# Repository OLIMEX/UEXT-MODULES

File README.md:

# UEXT-MODULES
OSHW UEXT modules

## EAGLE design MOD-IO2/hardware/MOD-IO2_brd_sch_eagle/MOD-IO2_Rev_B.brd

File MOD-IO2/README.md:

# MOD-IO2

**Input output expandable board with UEXT**

MOD-IO2 is a stackable development board which adds RELAYs and GPIOs to any of our development boards with UEXT.
If you work with any of our development boards with a [UEXT connector](https://www.olimex.com/Products/Modules/UEXT) and you need more GPIOs and/or RELAY outputs, you can add these by connecting MOD-IO2 to your development board.
This board gives you an easy way to interface up to 2 relays and 7 GPIOs.
MOD-IO2 is stackable and addressable, but what does this mean?
These boards can stack together so you can add as many inputs and outputs as you want!
E.g. 2-4-6-8 etc.!
MOD-IO2 has a PIC16F1503 microcontroller and the firmware is available for modification.

[Purchase your MOD-IO2 here!](https://www.olimex.com/Products/Modules/IO/MOD-IO2/open-source-hardware)

## FEATURES

- PIC16F1503 microcontroller
- Pre-loaded open-source firmware for easier interfacing, especially with Linux-enabled boards
- ICSP 6-pin connector for in-circuit programming with PIC-KIT3 or other compatible programmer/debugger.
- 9-pin terminal screw connector for 7 GPIOs, 3.3V and GND
- PWR jack for 12VDC
- 7 GPIOs which could implement different functionality as PWM, SPI, I2C, ANALOG IN/OUT etc.
- 2 relay outputs with 15A/250VAC contacts with screw terminals
- RELAY output status LEDs
- Four mounting holes - 3.3mm ~ (0.13)"
- FR-4, 1.5mm ~ (0.062)", soldermask, white silkscreen component print
- Dimensions 61x52mm ~ (2.4 x 2.05)"

## DOCUMENTS

- [MOD-IO2 user manual](doc/MOD-IO2.pdf)

## HARDWARE

- [MOD-IO2 schematic](hardware/MOD-IO2-Rev-B-schematic.pdf)
- [MOD-IO2 schematic and board layout sources for Eagle](hardware/MOD-IO2_brd_sch_eagle)

## SOFTWARE

- [MOD-IO2 firmware version 3.02](software/MOD-IO2_firmware_v_3_02)
- [Linux tool for controlling MOD-IO2](https://github.com/OLIMEX/OLINUXINO/tree/master/SOFTWARE/UEXT%20MODULES/MOD-IO2/linux-access-tool)
- [Arduino IDE library for MOD-IO2 + OLIMEXINO-328](software/OLIMEXINO-328+MOD-IO2)
- [OLIMEXINO-STM32 and MOD-IO2 relay control](software/Olimexino-STM32_MOD-IO2)
- Older firmware, older demo software, customer projects and more at the [wiki page](https://www.olimex.com/wiki/MOD-IO2)

## FAQ

### I found a very nice example of MOD-IO2 connected to another board on the internet. It doesn't work despite using the same setup as the author. What might be different?

There are number of firmware revisions that had been released for MOD-IO2.
You should ensure the example you have found used the same firmware revision of MOD-IO2 as the one you have on the module at the moment.
Each major firmware revision uses a different board address (for firmware revisions 3, 3.1, and 3.02, it is the same - 0x21) AND DIFFERENT PROTOCOL.
Each firmware has a README file inside the source archive that is available for download.
Refer to that README or the user manual for more information about the firmware.

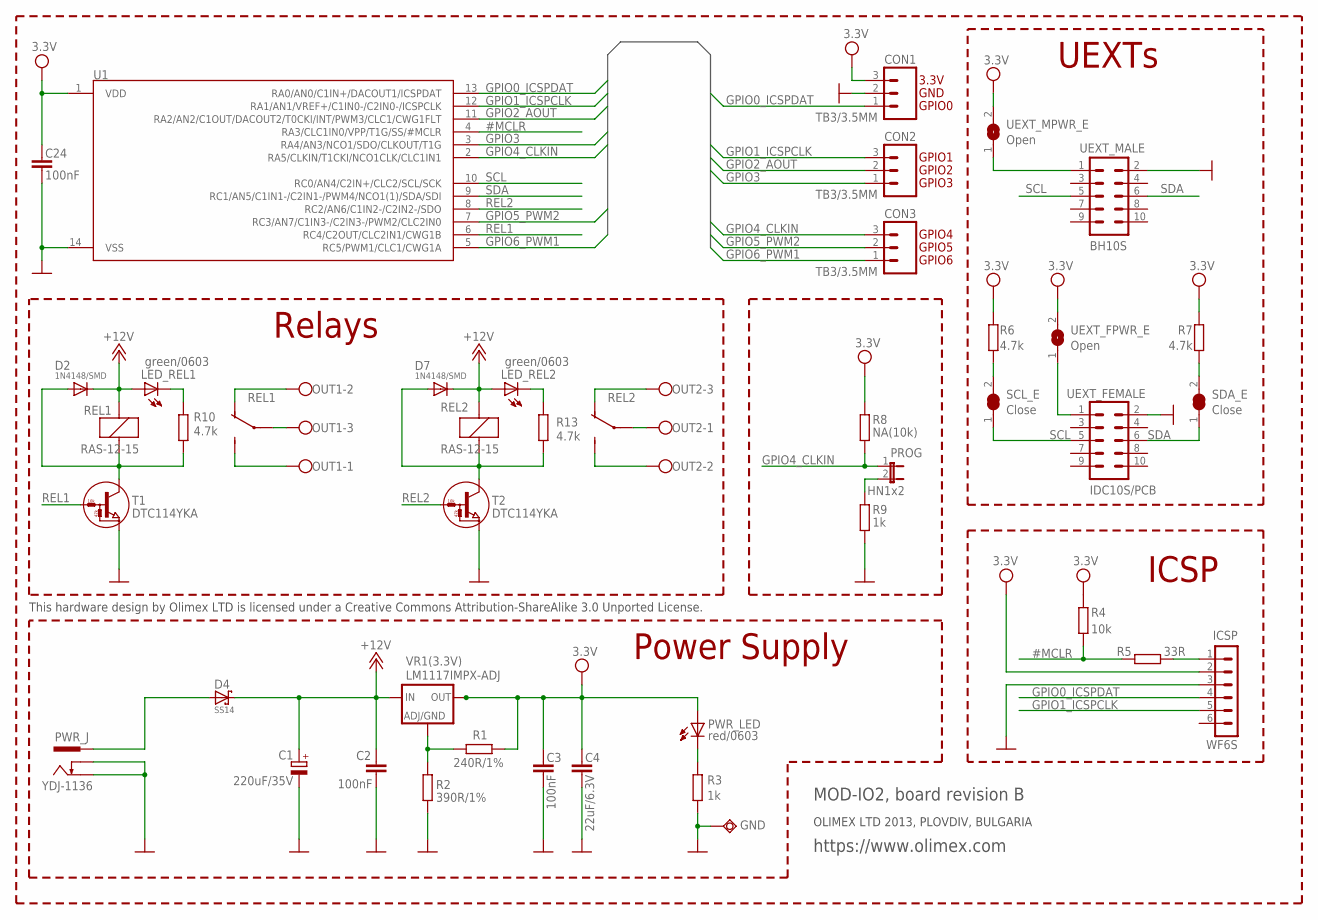
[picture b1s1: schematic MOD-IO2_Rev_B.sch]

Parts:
C1: 220uF/35V; E3,5-8
C2, C3, C24: 100nF; C0603_5MIL
C4: 22uF/6.3V; C0805_5MIL
CON1, CON2, CON3: TB3/3.5MM; CON3/3.5MM
D2, D7: 1N4148/SMD; SOD80C
D4: SS14; MLL-41
GND: TESTPAD40/70; TESTPAD
ICSP: WF6S
LED_REL1, LED_REL2: green/0603; LED-0603
OUT1, OUT2: TB3/5MM; W237-103
PROG: HN1x2; JP1
PWR_J: YDJ-1136; PWR_JACK_UNI_MILLING
PWR_LED: red/0603; LED-0603
R1: 240R/1%; R0603_5MIL
R2: 390R/1%; R0603_5MIL
R3, R9: 1k; R0603_5MIL
R4: 10k; R0603_5MIL
R5: 33R; R0603_5MIL
R6, R7, R10, R13: 4.7k; R0603_5MIL
R8: NA(10k); R0603_5MIL
REL1, REL2: RAS-12-15; H200-FAT
SCL_E: Close; SJ-CLOSE
SDA_E: Close; SJ-CLOSE
T1, T2: DTC114YKA; SOT-23
U1: PIC16F1503-I/SL; SOIC14
UEXT_FEMALE: IDC10S/PCB; ML10L_PADS_FEMAIL
UEXT_FPWR_E: Open; SJ
UEXT_MALE: BH10S; ML10_PADS
UEXT_MPWR_E: Open; SJ
VR1(3.3V): LM1117IMPX-ADJ; SOT223

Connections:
#MCLR: R4.2, R5.2, U1.4 (RA3/CLC1IN0/VPP/T1G/SS/#MCLR)
+12V: C1.+, C2.2, D2.C, D4.K (C), D7.C, LED_REL1.A, LED_REL2.A, REL1.1, REL2.1, VR1(3.3V).3 (IN)
ADJ/GND: R1.1, R2.1, VR1(3.3V).1 (ADJ/GND)
GND: C1.-, C2.1, C3.1, C4.1, C24.2, CON1.2, GND.P$1, ICSP.3, PWR_J.-, PWR_J.--, R2.2, R3.2, R9.1, T1.2 (E), T2.2 (E), U1.14 (VSS), UEXT_FEMALE.2, UEXT_MALE.2
GPIO0_ICSPDAT: CON1.1, ICSP.4, U1.13 (RA0/AN0/C1IN+/DACOUT1/ICSPDAT)
GPIO1_ICSPCLK: CON2.3, ICSP.5, U1.12 (RA1/AN1/VREF+/C1IN0-/C2IN0-/ICSPCLK)
GPIO2_AOUT: CON2.2, U1.11 (RA2/AN2/C1OUT/DACOUT2/T0CKI/INT/PWM3/CL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)
GPIO3: CON2.1, U1.3 (RA4/AN3/NCO1/SDO/CLKOUT/T1G)
GPIO4_CLKIN: CON3.3, PROG.1, R8.1, U1.2 (RA5/CLKIN/T1CKI/NCO1CLK/CLC1IN1)
GPIO5_PWM2: CON3.2, U1.7 (RC3/AN7/C1IN3-/C2IN3-/PWM2/CLC2IN0)
GPIO6_PWM1: CON3.1, U1.5 (RC5/PWM1/CLC1/CWG1A)
unnamed: OUT1.3, REL1.P
unnamed: UEXT_FEMALE.1, UEXT_FPWR_E.1
unnamed: OUT2.1, REL2.P
unnamed: OUT2.2, REL2.S
unnamed: R7.1, SDA_E.2
unnamed: R6.1, SCL_E.2
unnamed: OUT1.1, REL1.S
unnamed: PROG.2, R9.2
unnamed: UEXT_MALE.1, UEXT_MPWR_E.1
unnamed: ICSP.1, R5.1
unnamed: OUT2.3, REL2.O
unnamed: LED_REL1.C, R10.2
unnamed: OUT1.2, REL1.O
unnamed: LED_REL2.C, R13.2
unnamed: D7.A, R13.1, REL2.2, T2.3 (C)
unnamed: D2.A, R10.1, REL1.2, T1.3 (C)
unnamed: D4.A, PWR_J.+
unnamed: PWR_LED.C, R3.1
REL1: T1.1 (B), U1.6 (RC4/C2OUT/CLC2IN1/CWG1B)
REL2: T2.1 (B), U1.8 (RC2/AN6/C1IN2-/C2IN2-/SDO)
SCL: SCL_E.1, U1.10 (RC0/AN4/C2IN+/CLC2/SCL/SCK), UEXT_FEMALE.5, UEXT_MALE.5
SDA: SDA_E.1, U1.9 (RC1/AN5/C1IN1-/C2IN1-/PWM4/NCO1(1)/SDA/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), UEXT_FEMALE.6, UEXT_MALE.6
VCC: C3.2, C4.2, C24.1, CON1.3, ICSP.2, PWR_LED.A, R1.2, R4.1, R6.2, R7.2, R8.2, U1.1 (VDD), UEXT_FPWR_E.2, UEXT_MPWR_E.2, VR1(3.3V).2 (OUT), VR1(3.3V).4 (RAD)

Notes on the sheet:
ICSP
UEXTs
Power Supply
Relays
GPIO0
GPIO1
GPIO2
GPIO3
GPIO4
GPIO5
GPIO6
GND
3.3V
This hardware design by Olimex LTD is licensed under a Creative Commons Attribution-ShareAlike 3.0 Unported License.
OLIMEX LTD 2013, PLOVDIV, BULGARIA
https://www.olimex.com
MOD-IO2, board revision B

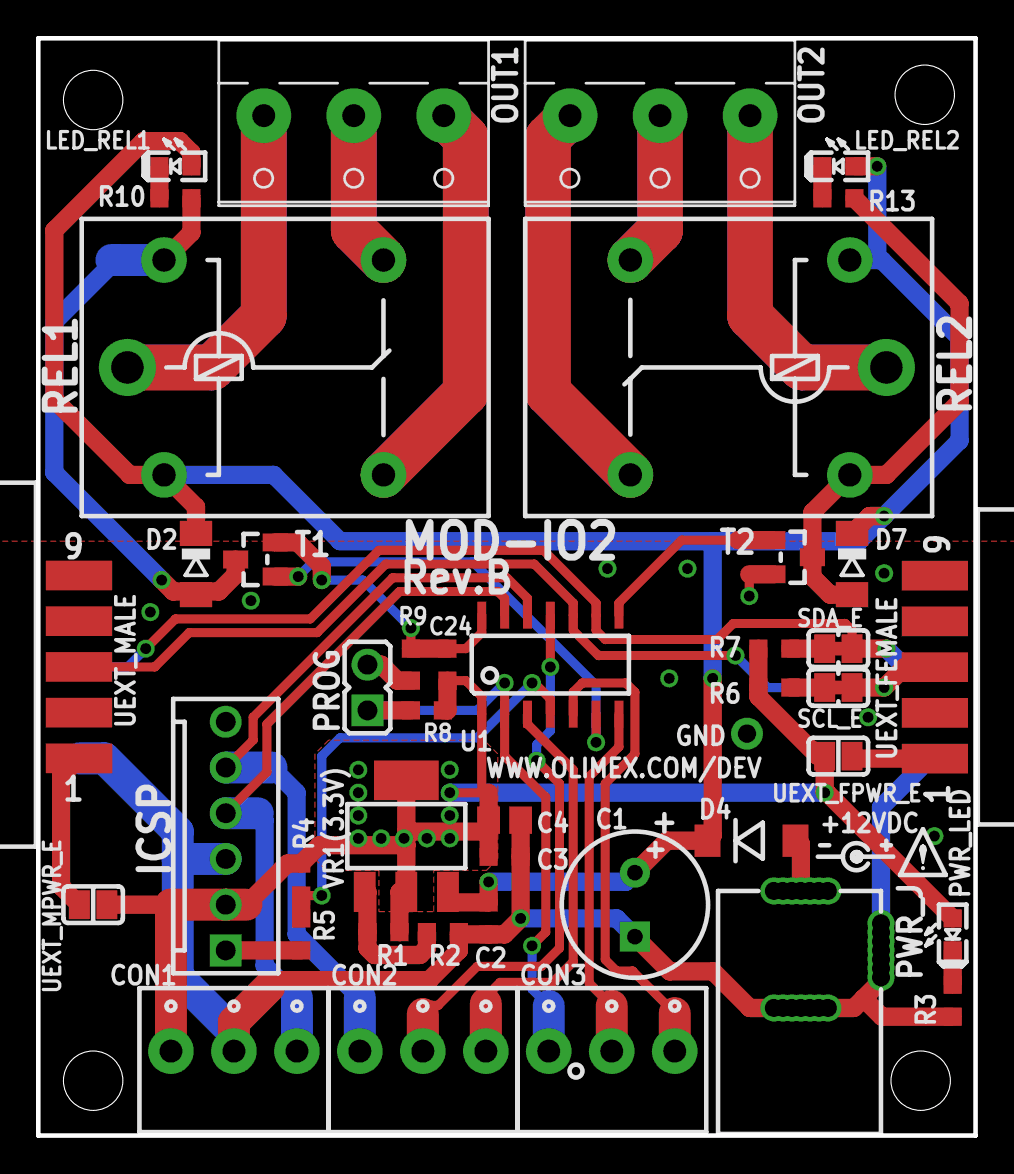
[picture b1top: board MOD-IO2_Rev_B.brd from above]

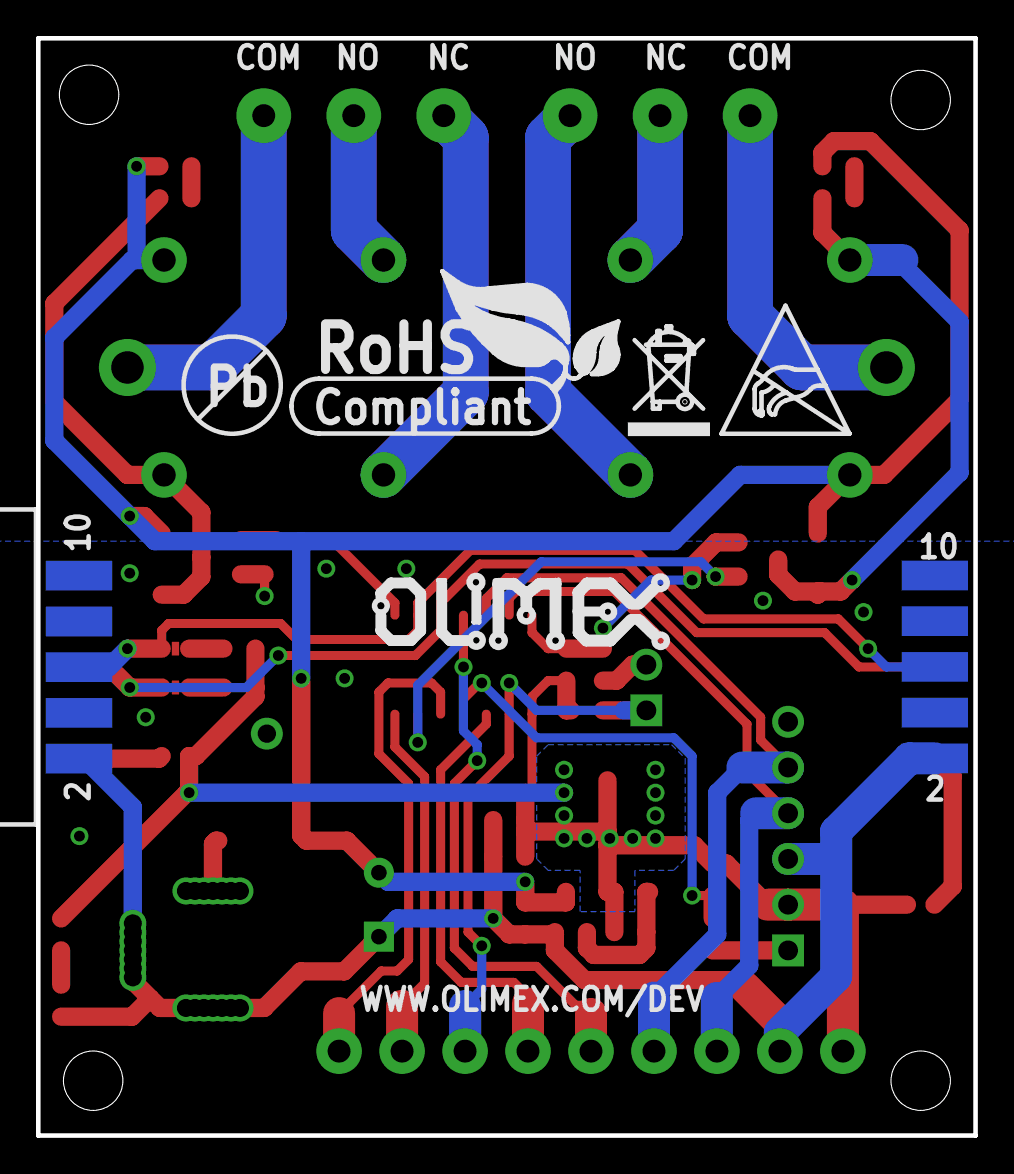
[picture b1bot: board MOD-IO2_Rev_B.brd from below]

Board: 2 copper layers, 52.1 x 61.0 mm, 49 parts (6 on the bottom side), 34 nets.

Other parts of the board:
U$1: RECYCLE_BIN1/8
U$3: ESD_SYMBOL
U$4: PB
U$5: ROHS
U$6: OLIMEX1_V
U$9: ATTENTION_SMALL

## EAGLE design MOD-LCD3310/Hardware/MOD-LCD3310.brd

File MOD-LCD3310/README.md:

MOD-LCD3310
===========

[
*MOD-LCD3310*](https://www.olimex.com/Products/Modules/LCD/MOD-LCD3310/open-source-hardware)

Hardware
--------
* Schematic in PDF format
* Schematic in Eagle format
* Board in Eagle format

Software
--------
* [**A20-OLinuXino-MICRO example**](https://github.com/OLIMEX/OLINUXINO/tree/master/SOFTWARE/A20)
* OLIMEXINO-32U4 (Arduino AVR) example
* PIC32-PINGUINO (PIC32) examples with GPIO and SPI
* OLIMEXINO-STM32 (Maple STM32) examples wigh GPIO and SPI
* NXP (LPC1227) example
* IAR (STM32) example

Licensee
--------
Apache License Version 2.0

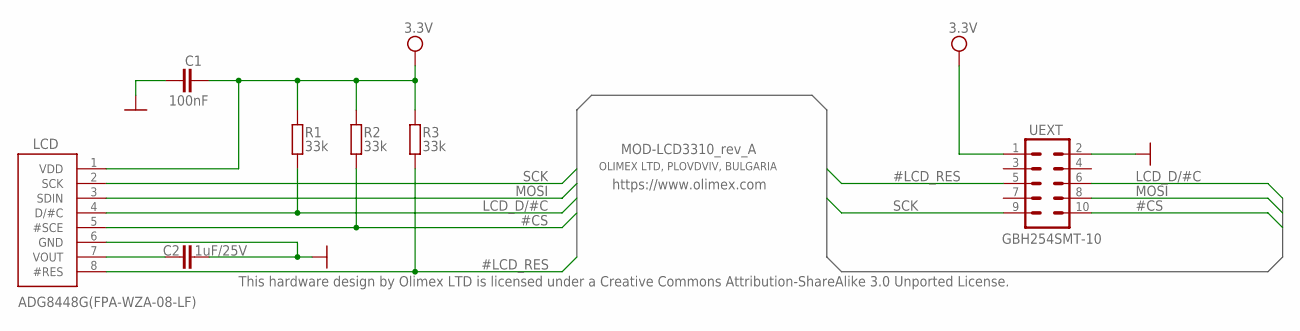
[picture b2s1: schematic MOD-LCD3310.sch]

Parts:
C1: 100nF; C0603_DWS
C2: 1uF/25V; C0805_5MIL_DWS
LCD: ADG8448G(FPA-WZA-08-LF); NOKIA_3310_LCD_CON8_EXACTLY_BOT
R1, R2, R3: 33k; R0603_5MIL_DWS
UEXT: GBH254SMT-10; ML10_S

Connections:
#CS: LCD.5 (#SCE), R2.2, UEXT.10
#LCD_RES: LCD.8 (#RES), R3.2, UEXT.5
GND: C1.2, C2.1, LCD.6 (GND), UEXT.2
LCD_D/#C: LCD.4 (D/#C), R1.2, UEXT.6
LCD_VOUT: C2.2, LCD.7 (VOUT)
MOSI: LCD.3 (SDIN), UEXT.8
SCK: LCD.2 (SCK), UEXT.9
VCC: C1.1, LCD.1 (VDD), R1.1, R2.1, R3.1, UEXT.1

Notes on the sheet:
MOD-LCD3310_rev_A
OLIMEX LTD, PLOVDVIV, BULGARIA
https://www.olimex.com
This hardware design by Olimex LTD is licensed under a Creative Commons Attribution-ShareAlike 3.0 Unported License.

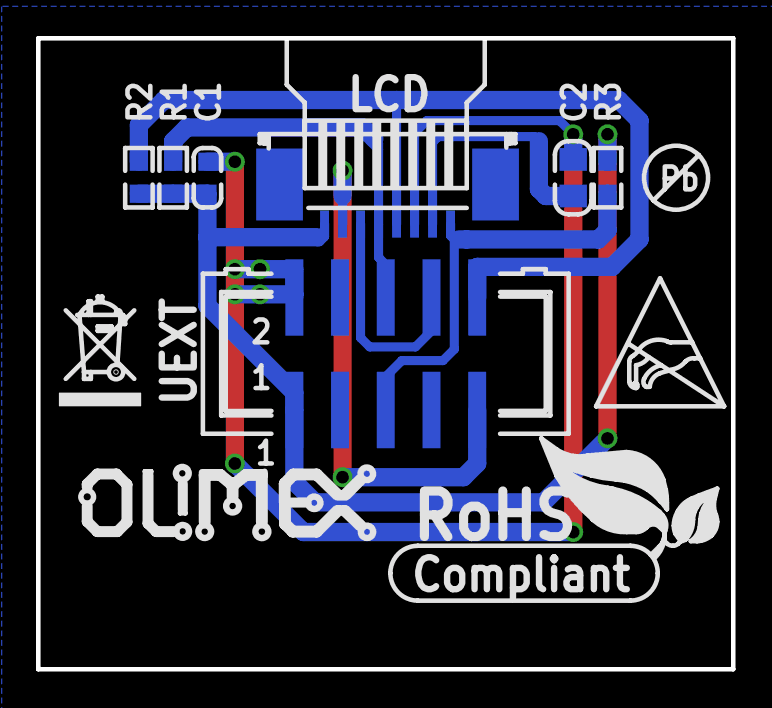
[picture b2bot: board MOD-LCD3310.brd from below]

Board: 2 copper layers, 38.6 x 35.1 mm, 12 parts (11 on the bottom side), 8 nets.

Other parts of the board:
U$1: PB_SMALL
U$2: RECYCLE_BIN1/8
U$3: ESD_SYMBOL
U$4: ROHS
U$8: OLIMEX1_V

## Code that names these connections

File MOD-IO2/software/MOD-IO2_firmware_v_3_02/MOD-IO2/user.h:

/******************************************************************************/
/* User Level #define Macros                                                  */
/******************************************************************************/

#define REL1	LATCbits.LATC4
#define REL2	LATCbits.LATC2
#define REL1_TRIS TRISCbits.TRISC4
#define REL2_TRIS TRISCbits.TRISC2


#define GPIO0_TRIS TRISAbits.TRISA0
#define GPIO0_LAT LATAbits.LATA0
#define GPIO0_PORT PORTAbits.RA0

#define GPIO1_TRIS TRISAbits.TRISA1
#define GPIO1_LAT LATAbits.LATA1
#define GPIO1_PORT PORTAbits.RA1

#define GPIO2_TRIS TRISAbits.TRISA2
#define GPIO2_LAT LATAbits.LATA2
#define GPIO2_PORT PORTAbits.RA2

#define GPIO3_TRIS TRISAbits.TRISA4
#define GPIO3_LAT LATAbits.LATA4
#define GPIO3_PORT PORTAbits.RA4

#define GPIO4_TRIS TRISAbits.TRISA5
#define GPIO4_LAT LATAbits.LATA5
#define GPIO4_PORT PORTAbits.RA5

#define GPIO5_TRIS TRISCbits.TRISC3
#define GPIO5_LAT LATCbits.LATC3
#define GPIO5_PORT PORTCbits.RC3

#define GPIO6_TRIS TRISCbits.TRISC5
#define GPIO6_LAT LATCbits.LATC5
#define GPIO6_PORT PORTCbits.RC5


#define JMP_TRIS	TRISAbits.TRISA5
#define JMP_LAT		LATAbits.LATA5
#define JMP_PORT	PORTAbits.RA5

/*--------------------------------I2C PINS--------------------------------*/
#define SCL_TRIS		TRISCbits.TRISC0
#define SCL_LAT			LATCbits.LATC0
#define SCL_PORT		PORTCbits.RC0
#define SDA_TRIS		TRISCbits.TRISC1
#define SDA_LAT			LATCbits.LATC1
#define SDA_PORT		PORTCbits.RC1

#define DEFAULT_ADDRESS		0x21
#define MEMORY_ADDRESS		0x7FF

#define START_C	0b00001000	//START CONDITION MASK
#define STOP_C	0b00010000	//STOP CONDITION MASK
#define STATE1	0b00001001	// MASTER WRITE LAST WAS ADDRESS
#define STATE2	0b00101001	// MASTER WRITE LAST WAS DATA
#define STATE3	0b00001101	// MASTER READ LAST WAS ADDRESS
#define STATE4	0b00101100	// MASTER READ LAST WAS DATA
#define STATE5	0b00101000	// MASTER NACK

#define MAX_BUFFER_SIZE		10


#define Nop() asm("NOP")


/******************************************************************************/
/* Local Variables							      */
/******************************************************************************/

extern unsigned char ADDRESS;
extern unsigned char DATA_BUFFER[6];
extern unsigned int DATA_INDEX;
extern unsigned char DATA_OUT[2];



/******************************************************************************/
/* User Function Prototypes                                                   */
/******************************************************************************/



/**
 * Initialize all the periphere
 * @param none
 */
void InitApp(void);
/**
 * Read stored address from the program memmory 0x7FF. If the cell if empty
 * the board load the default address - 0x21.
 * @param none
 */
void InitAddress(void);
/**
 * Initialize all the gpio ports. By default:
 * @LAT registers - All "0" - low level
 * @TRIS registers - All "1" - inputs
 * @WPUA registers - All pullups on PORTA are on, PORTC doesn't have such.
 * @param none
 */
void InitGPIO(void);
/**
 * Initialize interrupts. Only interrupts from I2C are processed.
 * @param none
 */
void InitInterupts(void);
/**
 * Initialize I2C module. It is configured for 100kHz, 7-bit address, with
 * enabled clock streching and enabled STOP and START interrupts.
 * @param none
 */
void InitI2C(void);
/**
 * Write procedure for writing in the program memory.
 * @param data Data to be stored, the range is from 0x0000 to 0x3FFF.
 * @param address The address of the cell in the programm memory.
 */
void WriteFlash(unsigned int data, unsigned int address);
/**
 * Read procedure for reading from the program memory.
 * @return The data in the selected cell
 * @param address The address of the cell in the program memory.
 */
unsigned int ReadFlash(unsigned int address);
/**
 * Erase the stored data in specific cell int the program memory.
 * @param address The address of the cell
 */
void EraseFlash(unsigned int address);
/**
 * By unlocking the cell becomes available for writing and erasing.
 * @param none
 */
void UnlockFlash(void);
/*
 * Defines the function of the gpio.
 * @param data - The states of all gpios bit0 - GPIO0, bit1 - GPIO1 ...
 */
void CommandSetTris(unsigned char data);
/**
 * Set output level of the gpios
 * @param data - Defines all parameters - bit0 - GPIO0, bit1 - GPIO1 ...
 */
void CommandSetLat(unsigned char data);
/**
 * Return the current state of the PORT registers.
 * @param none
 */
unsigned char CommandGetPort(void);
/**
 * Set or clear pullups. Note that not all GPIO have internal pullups.
 * @param data - bitmasked state of the all GPIOs pullups
 */
void CommandSetPullUps(unsigned char data);
/* Set state of the two relays.
 * @param data - bitmasked state of the relays - bit0 -REL1, bit1 - REL2.
 */
void CommandSetRelay(unsigned char data);
/**
 * Set new address for this device. PROG jumper must closed to set new address.
 * @param addr - The new address.
 */
void CommandSetOnX(unsigned char data);
/* Switch Relay ON 1 - relay1, 2 - relay2, 3 - both*/
void CommandSetOffX(unsigned char data);
/* Switch Relay OFF 1 - relay1, 2 - relay2, 3 - both*/
void CommandSetAddress(unsigned char data);
/**
 * Change i2c address! Jumper 1 must be closed.
 * @param none
 */
unsigned char CommandGetTris(void);
/**
 * Return the current stsate of the LAT registers.
 * @param none
 */
unsigned char CommandGetLat(void);
/**
 * Return the readings from Analog input
 * @param channel The analog channel to select.
 */
unsigned int CommandGetAnalog(unsigned char channel);


void SetPWM1(unsigned char value);
/*
 *   value = pwm duty  
 */
void SetPWM2(unsigned char value);
/*
 * value = pwm duty 
 */
void ClosePWM(unsigned char value);
/*
 * value = pwm# to be closed
 */

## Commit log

2015-03-12 MOD-MPU9150 and MOD-OLED-128x64
2015-05-28 MOD-LCD3310 files and examples
2015-05-28 Updated few examples
2015-05-28 Example updates
2015-05-29 Updated few of the files
2015-07-03 Added more modules and examples
2018-10-29 Add MOD-IO2 resources, exactly from Olimex product page
2018-10-29 Add product image from product page
2018-10-29 Fix image path
2018-10-29 Improve subsection aesthetic
2018-12-03 adc0 read corrected
2021-10-05 lcd3310: clarify and simplify pin changes
    For the ESP-PoE-ISO I had to change the pin numberings.
    They were originally as follows, but it was unclear what hardware they were for.
    MOSI=16
    SCK=15
    CS=13
    RES=3

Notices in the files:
MOD-LCD3310/Hardware/MOD-LCD3310.brd:
(C) 2011
